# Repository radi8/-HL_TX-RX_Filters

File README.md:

# HL_TX-RX_Filters
Transmit and receive filters catalog plus Kicad layout for 100 x 100 mm PCB and part listings

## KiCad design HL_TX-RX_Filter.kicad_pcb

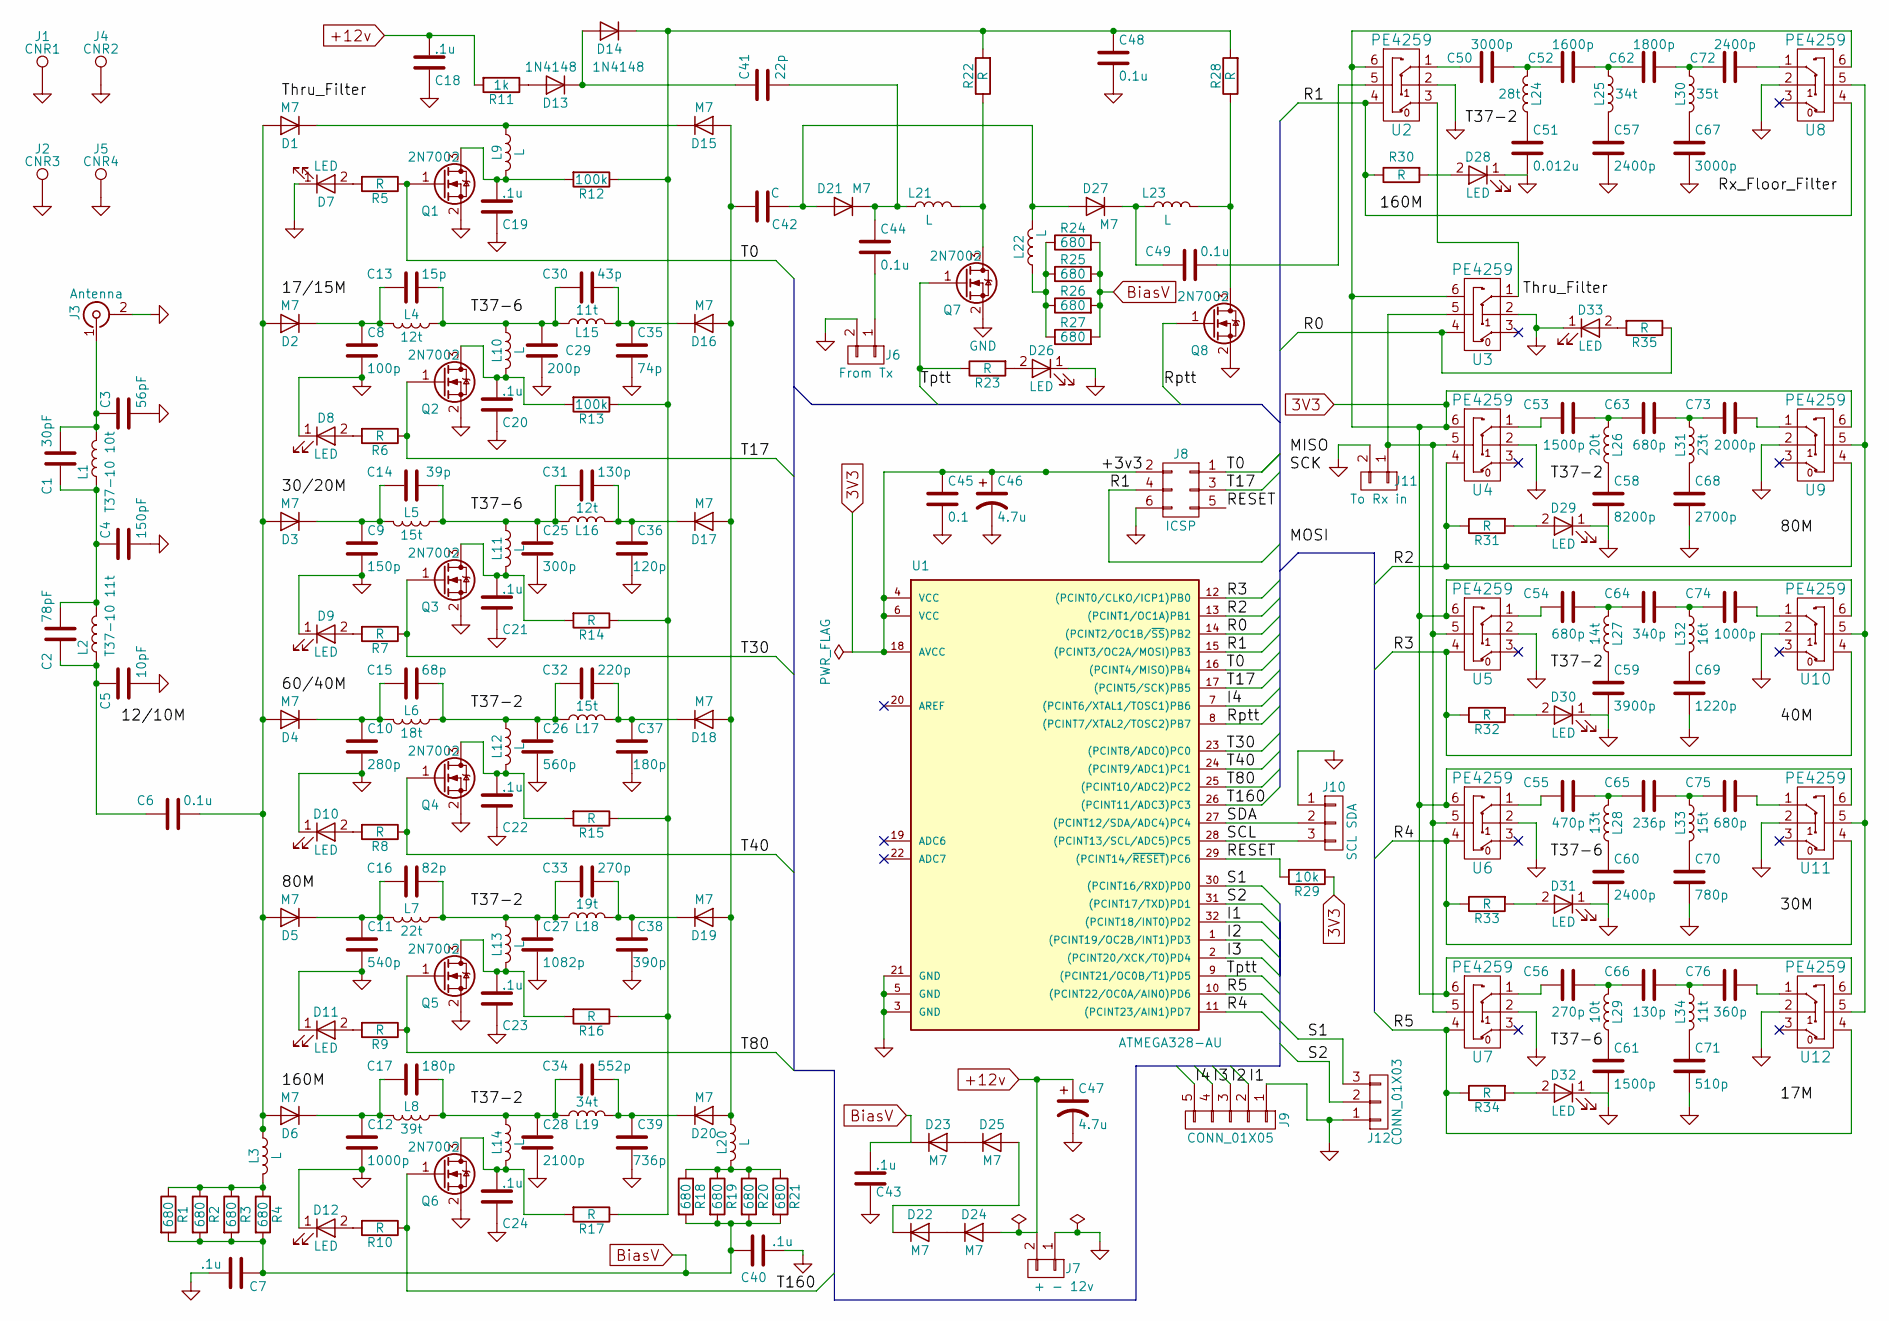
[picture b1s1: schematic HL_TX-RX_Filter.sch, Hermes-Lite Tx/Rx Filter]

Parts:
C1: 30pF; C_1206_HandSoldering
C2: 78pF; C_1206_HandSoldering
C3: 56pF; C_1206_HandSoldering
C4: 150pF; C_1206_HandSoldering
C5: 10pF; C_1206_HandSoldering
C6, C44, C48, C49: 0.1u; C_1206_HandSoldering
C7, C18, C19, C20, C21, C22, C23, C24, C40, C43: .1u; C_1206_HandSoldering
C8: 100p; C_1206_HandSoldering
C9: 150p; C_1206_HandSoldering
C10: 280p; C_1206_HandSoldering
C11: 540p; C_1206_HandSoldering
C12, C74: 1000p; C_1206_HandSoldering
C13: 15p; C_1206_HandSoldering
C14: 39p; C_1206_HandSoldering
C15: 68p; C_1206_HandSoldering
C16: 82p; C_1206_HandSoldering
C17, C37: 180p; C_1206_HandSoldering
C25: 300p; C_1206_HandSoldering
C26: 560p; C_1206_HandSoldering
C27: 1082p; C_1206_HandSoldering
C28: 2100p; C_1206_HandSoldering
C29: 200p; C_1206_HandSoldering
C30: 43p; C_1206_HandSoldering
C31, C66: 130p; C_1206_HandSoldering
C32: 220p; C_1206_HandSoldering
C33, C56: 270p; C_1206_HandSoldering
C34: 552p; C_1206_HandSoldering
C35: 74p; C_1206_HandSoldering
C36: 120p; C_1206_HandSoldering
C38: 390p; C_1206_HandSoldering
C39: 736p; C_1206_HandSoldering
C41: 22p; C_1206_HandSoldering
C42: C; C_1206_HandSoldering
C45: 0.1; C_1206_HandSoldering
C46, C47: 4.7u; CP_Radial_D5.0mm_P2.00mm
C50, C67: 3000p; C_1206_HandSoldering
C51: 0.012u; C_1206_HandSoldering
C52: 1600p; C_1206_HandSoldering
C53, C61: 1500p; C_1206_HandSoldering
C54, C63, C75: 680p; C_1206_HandSoldering
C55: 470p; C_1206_HandSoldering
C57, C60, C72: 2400p; C_1206_HandSoldering
C58: 8200p; C_1206_HandSoldering
C59: 3900p; C_1206_HandSoldering
C62: 1800p; C_1206_HandSoldering
C64: 340p; C_1206_HandSoldering
C65: 236p; C_1206_HandSoldering
C68: 2700p; C_1206_HandSoldering
C69: 1220p; C_1206_HandSoldering
C70: 780p; C_1206_HandSoldering
C71: 510p; C_1206_HandSoldering
C73: 2000p; C_1206_HandSoldering
C76: 360p; C_1206_HandSoldering
D1, D2, D3, D4, D5, D6, D15, D16, D17, D18, D19, D20, D21, D27: M7; D_SMA_Handsoldering
D7, D8, D9, D10, D11, D12, D26, D28, D29, D30, D31, D32, D33: LED; LED_1206
D13, D14: 1N4148; D_MiniMELF_Handsoldering
D22, D23, D24, D25: M7; D_SMA
J1: CNR1; 1pin
J2: CNR3; 1pin
J3: Antenna; SMAEDGE_TH
J4: CNR2; 1pin
J5: CNR4; 1pin
J6: From Tx; Pin_Header_Straight_1x02_Pitch2.54mm
J7: + - 12v; Pin_Header_Straight_1x02_Pitch2.54mm
J8: ICSP; Pin_Header_Straight_2x03_Pitch2.54mm
J9: CONN_01X05; Pin_Header_Straight_1x05_Pitch2.54mm
J10: SCL SDA; Pin_Header_Straight_1x03_Pitch2.54mm
J11: To Rx in; Pin_Header_Straight_1x02_Pitch2.54mm
J12: CONN_01X03; Pin_Header_Straight_1x03_Pitch2.54mm
L1: T37-10 10t; Toroid_T37_Vertical
L2: T37-10 11t; Toroid_T37_Vertical
L3, L9, L10, L11, L12, L13, L14, L20, L21, L22, L23: L; L_1812_HandSoldering
L4, L16: 12t; Toroid_T37_Vertical
L5, L17, L33: 15t; Toroid_T37_Vertical
L6: 18t; Toroid_T37_Vertical
L7: 22t; Toroid_T37_Vertical
L8: 39t; Toroid_T37_Vertical
L15, L34: 11t; Toroid_T37_Vertical
L18: 19t; Toroid_T37_Vertical
L19, L25: 34t; Toroid_T37_Vertical
L24: 28t; Toroid_T37_Vertical
L26: 20t; Toroid_T37_Vertical
L27: 14t; Toroid_T37_Vertical
L28: 13t; Toroid_T37_Vertical
L29: 10t; Toroid_T37_Vertical
L30: 35t; Toroid_T37_Vertical
L31: 23t; Toroid_T37_Vertical
L32: 16t; Toroid_T37_Vertical
Q1, Q2, Q3, Q4, Q5, Q6, Q7, Q8: 2N7002; SOT-23
R1, R2, R3, R4, R18, R19, R20, R21, R24, R25, R26, R27: 680; R_1206_HandSoldering
R5, R6, R7, R8, R9, R10, R14, R15, R16, R17, R22, R23, R28, R30, R31, R32, R33, R34, R35: R; R_1206_HandSoldering
R11: 1k; R_1206_HandSoldering
R12, R13: 100k; R_1206_HandSoldering
R29: 10k; R_1206_HandSoldering
U1: ATMEGA328-AU; TQFP-32_7x7mm_Pitch0.8mm
U2, U3, U4, U5, U6, U7, U8, U9, U10, U11, U12: PE4259; SOT-363_SC-70-6_Handsoldering

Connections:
3V3: C45.1, C46.1, J8.2, R29.1, U1.4 (VCC), U1.6 (VCC), U1.18 (AVCC), U2.6, U3.6, U4.6, U5.6, U6.6, U7.6, U8.6, U9.6, U10.6, U11.6, U12.6
+12v: C18.1, C47.1, D24.2 (A), J7.2, R11.2
/I1: J9.2, U1.32 ((PCINT18/INT0)PD2)
/I2: J9.3, U1.1 ((PCINT19/OC2B/INT1)PD3)
/I3: J9.4, U1.2 ((PCINT20/XCK/T0)PD4)
/I4: J9.5, U1.7 ((PCINT6/XTAL1/TOSC1)PB6)
/R0: R35.1, U1.14 ((PCINT2/OC1B/~SS~)PB2), U3.4
/R1: J8.4, R30.1, U1.15 ((PCINT3/OC2A/MOSI)PB3), U2.4, U8.4
/R2: R31.1, U1.13 ((PCINT1/OC1A)PB1), U4.4, U9.4
/R3: R32.1, U1.12 ((PCINT0/CLKO/ICP1)PB0), U5.4, U10.4
/R4: R33.1, U1.11 ((PCINT23/AIN1)PD7), U6.4, U11.4
/R5: R34.1, U1.10 ((PCINT22/OC0A/AIN0)PD6), U7.4, U12.4
/RESET: J8.5, R29.2, U1.29 ((PCINT14/~RESET~)PC6)
/Rptt: Q8.1 (G), U1.8 ((PCINT7/XTAL2/TOSC2)PB7)
/S1: J12.3, U1.30 ((PCINT16/RXD)PD0)
/S2: J12.2, U1.31 ((PCINT17/TXD)PD1)
/SCL: J10.3, U1.28 ((PCINT13/SCL/ADC5)PC5)
/SDA: J10.2, U1.27 ((PCINT12/SDA/ADC4)PC4)
/T0: J8.1, Q1.1 (G), R5.1, U1.16 ((PCINT4/MISO)PB4)
/T17: J8.3, Q2.1 (G), R6.1, U1.17 ((PCINT5/SCK)PB5)
/T30: Q3.1 (G), R7.1, U1.23 ((PCINT8/ADC0)PC0)
/T40: Q4.1 (G), R8.1, U1.24 ((PCINT9/ADC1)PC1)
/T80: Q5.1 (G), R9.1, U1.25 ((PCINT10/ADC2)PC2)
/T160: Q6.1 (G), R10.1, U1.26 ((PCINT11/ADC3)PC3)
/Tptt: Q7.1 (G), R23.1, U1.9 ((PCINT21/OC0B/T1)PD5)
BiasV: C7.2, C40.2, C43.1, D23.1 (K), R1.2, R2.2, R3.2, R4.2, R18.2, R19.2, R20.2, R21.2, R24.2, R25.2, R26.2, R27.2
GND: C3.2, C4.2, C5.2, C7.1, C8.2, C9.2, C10.2, C11.2, C12.2, C18.2, C19.2, C20.2, C21.2, C22.2, C23.2, C24.2, C25.2, C26.2, C27.2, C28.2, C29.2, C35.2, C36.2, C37.2, C38.2, C39.2, C40.1, C43.2, C45.2, C46.2, C47.2, C48.2, C51.2, C57.2, C58.2, C59.2, C60.2, C61.2, C67.2, C68.2, C69.2, C70.2, C71.2, D7.1 (K), D8.1 (K), D9.1 (K), D10.1 (K), D11.1 (K), D12.1 (K), D26.1 (K), D28.1 (K), D29.1 (K), D30.1 (K), D31.1 (K), D32.1 (K), D33.1 (K), J1.1, J2.1, J3.2 (Ext), J4.1, J5.1, J6.2, J7.1, J8.6, J9.1, J10.1, J11.2, J12.1, Q1.2 (S), Q2.2 (S), Q3.2 (S), Q4.2 (S), Q5.2 (S), Q6.2 (S), Q7.2 (S), Q8.2 (S), U1.3 (GND), U1.5 (GND), U1.21 (GND), U2.2, U3.2, U4.2, U5.2, U6.2, U7.2, U8.2, U9.2, U10.2, U11.2, U12.2
unnamed: C1.1, C2.2, C4.1, L1.1, L2.2
unnamed: C1.2, C3.1, J3.1 (In), L1.2
unnamed: C2.1, C5.1, C6.1, L2.1
unnamed: C6.2, D1.2 (A), D2.2 (A), D3.2 (A), D4.2 (A), D5.2 (A), D6.2 (A), L3.1
unnamed: C10.1, C15.1, D4.1 (K), L6.2
unnamed: C11.1, C16.1, D5.1 (K), L7.2
unnamed: C12.1, C17.1, D6.1 (K), L8.2
unnamed: C8.1, C13.1, D2.1 (K), L4.2
unnamed: C13.2, C29.1, C30.1, L4.1, L10.1, L15.1
unnamed: C9.1, C14.1, D3.1 (K), L5.2
unnamed: C14.2, C25.1, C31.1, L5.1, L11.1, L16.1
unnamed: C15.2, C26.1, C32.1, L6.1, L12.1, L17.1
unnamed: C16.2, C27.1, C33.1, L7.1, L13.1, L18.1
unnamed: C17.2, C28.1, C34.1, L8.1, L14.1, L19.1
unnamed: C19.1, L9.2, Q1.3 (D), R12.2
unnamed: C20.1, L10.2, Q2.3 (D), R13.2
unnamed: C21.1, L11.2, Q3.3 (D), R14.2
unnamed: C22.1, L12.2, Q4.3 (D), R15.2
unnamed: C23.1, L13.2, Q5.3 (D), R16.2
unnamed: C24.1, L14.2, Q6.3 (D), R17.2
unnamed: C30.2, C35.1, D16.1 (K), L15.2
unnamed: C31.2, C36.1, D17.1 (K), L16.2
unnamed: C32.2, C37.1, D18.1 (K), L17.2
unnamed: C33.2, C38.1, D19.1 (K), L18.2
unnamed: C34.2, C39.1, D20.1 (K), L19.2
unnamed: C41.1, D13.1 (K), D14.2 (A)
unnamed: C41.2, C44.1, D21.1 (K), L21.1
unnamed: C42.1, D15.2 (A), D16.2 (A), D17.2 (A), D18.2 (A), D19.2 (A), D20.2 (A), L20.1
unnamed: C42.2, D21.2 (A), D27.2 (A), L22.2
unnamed: C44.2, J6.1
unnamed: C48.1, D14.1 (K), R12.1, R13.1, R14.1, R15.1, R16.1, R17.1, R22.2, R28.2
unnamed: C49.1, D27.1 (K), L23.1
unnamed: C49.2, U2.5
unnamed: C50.1, U2.1
unnamed: C50.2, C52.1, L24.2
unnamed: C51.1, L24.1
unnamed: C52.2, C62.1, L25.1
unnamed: C53.1, U4.1
unnamed: C53.2, C63.1, L26.2
unnamed: C54.1, U5.1
unnamed: C54.2, C64.1, L27.2
unnamed: C55.1, U6.1
unnamed: C55.2, C65.1, L28.2
unnamed: C56.1, U7.1
unnamed: C56.2, C66.1, L29.2
unnamed: C57.1, L25.2
unnamed: C58.1, L26.1
unnamed: C59.1, L27.1
unnamed: C60.1, L28.1
unnamed: C61.1, L29.1
unnamed: C62.2, C72.1, L30.1
unnamed: C63.2, C73.1, L31.1
unnamed: C64.2, C74.1, L32.1
unnamed: C65.2, C75.1, L33.1
unnamed: C66.2, C76.1, L34.1
unnamed: C67.1, L30.2
unnamed: C68.1, L31.2
unnamed: C69.1, L32.2
unnamed: C70.1, L33.2
unnamed: C71.1, L34.2
unnamed: C72.2, U8.1
unnamed: C73.2, U9.1
unnamed: C74.2, U10.1
unnamed: C75.2, U11.1
unnamed: C76.2, U12.1
unnamed: D1.1 (K), D15.1 (K), L9.1
unnamed: D7.2 (A), R5.2
unnamed: D8.2 (A), R6.2
unnamed: D9.2 (A), R7.2
unnamed: D10.2 (A), R8.2
unnamed: D11.2 (A), R9.2
unnamed: D12.2 (A), R10.2
unnamed: D13.2 (A), R11.1
unnamed: D22.1 (K), D25.2 (A)
unnamed: D22.2 (A), D24.1 (K)
unnamed: D23.2 (A), D25.1 (K)
unnamed: D26.2 (A), R23.2
unnamed: D28.2 (A), R30.2
unnamed: D29.2 (A), R31.2
unnamed: D30.2 (A), R32.2
unnamed: D31.2 (A), R33.2
unnamed: D32.2 (A), R34.2
unnamed: D33.2 (A), R35.2
unnamed: J11.1, U3.5, U4.5, U5.5, U6.5, U7.5
unnamed: L3.2, R1.1, R2.1, R3.1, R4.1
unnamed: L20.2, R18.1, R19.1, R20.1, R21.1
unnamed: L21.2, Q7.3 (D), R22.1
unnamed: L22.1, R24.1, R25.1, R26.1, R27.1
unnamed: L23.2, Q8.3 (D), R28.1
unnamed: U2.3, U3.1
unnamed: U8.5, U9.5, U10.5, U11.5, U12.5

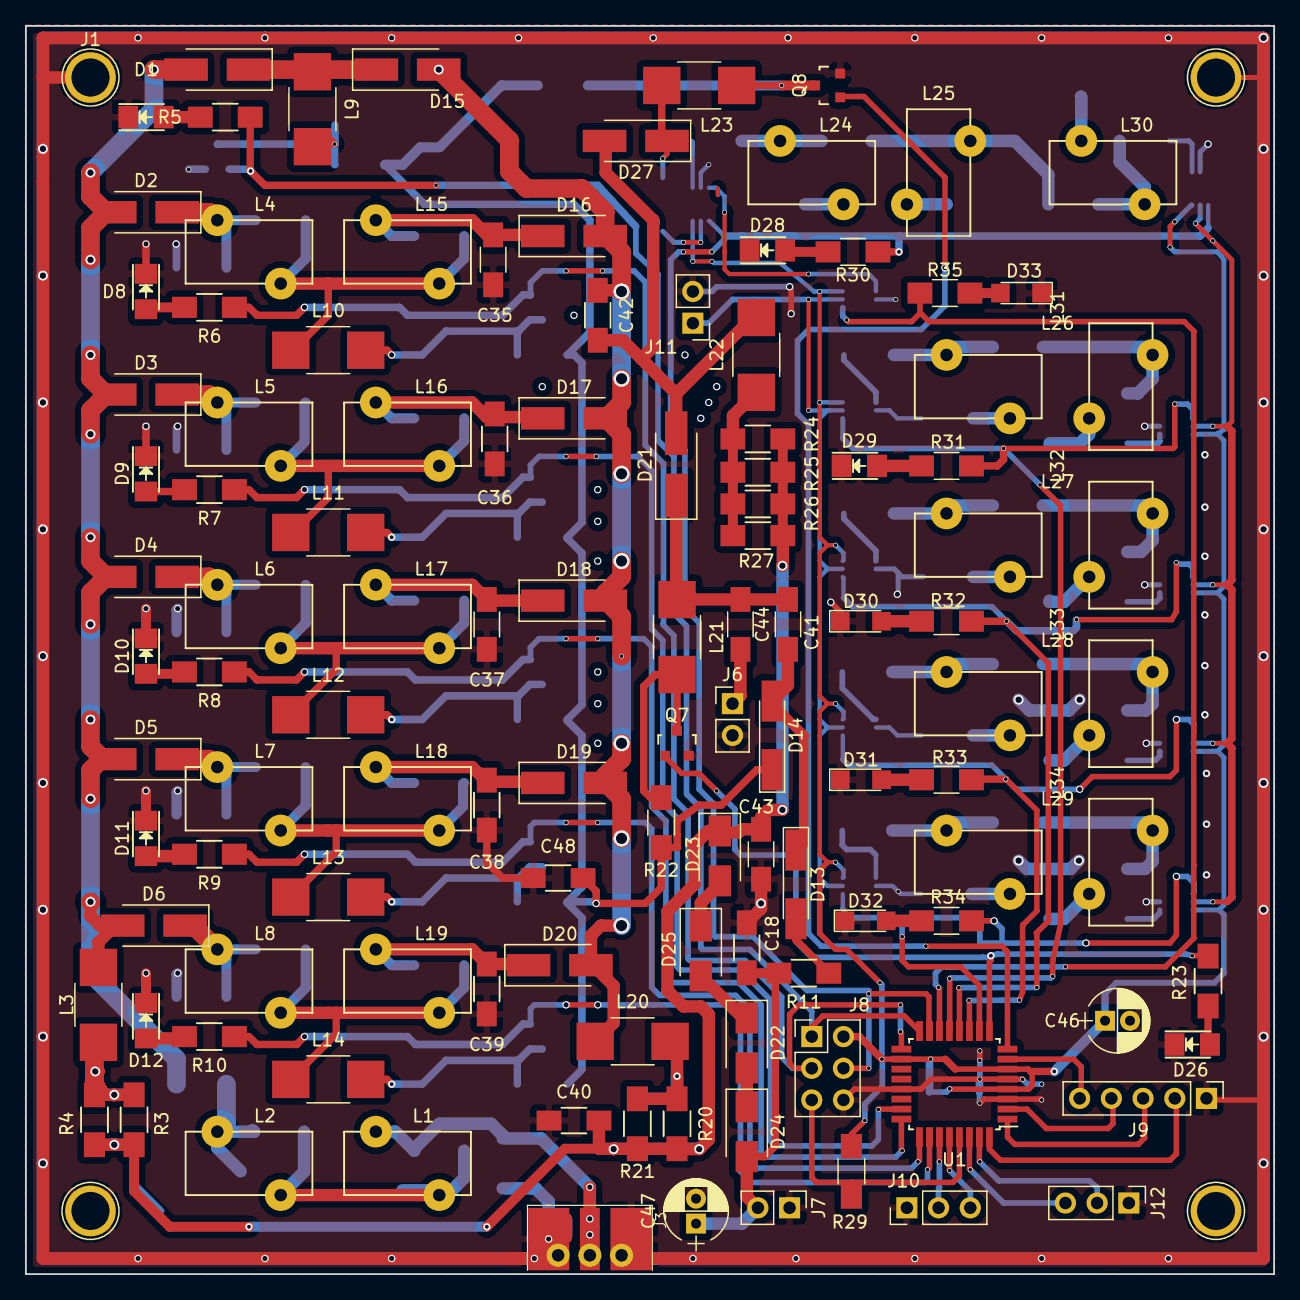
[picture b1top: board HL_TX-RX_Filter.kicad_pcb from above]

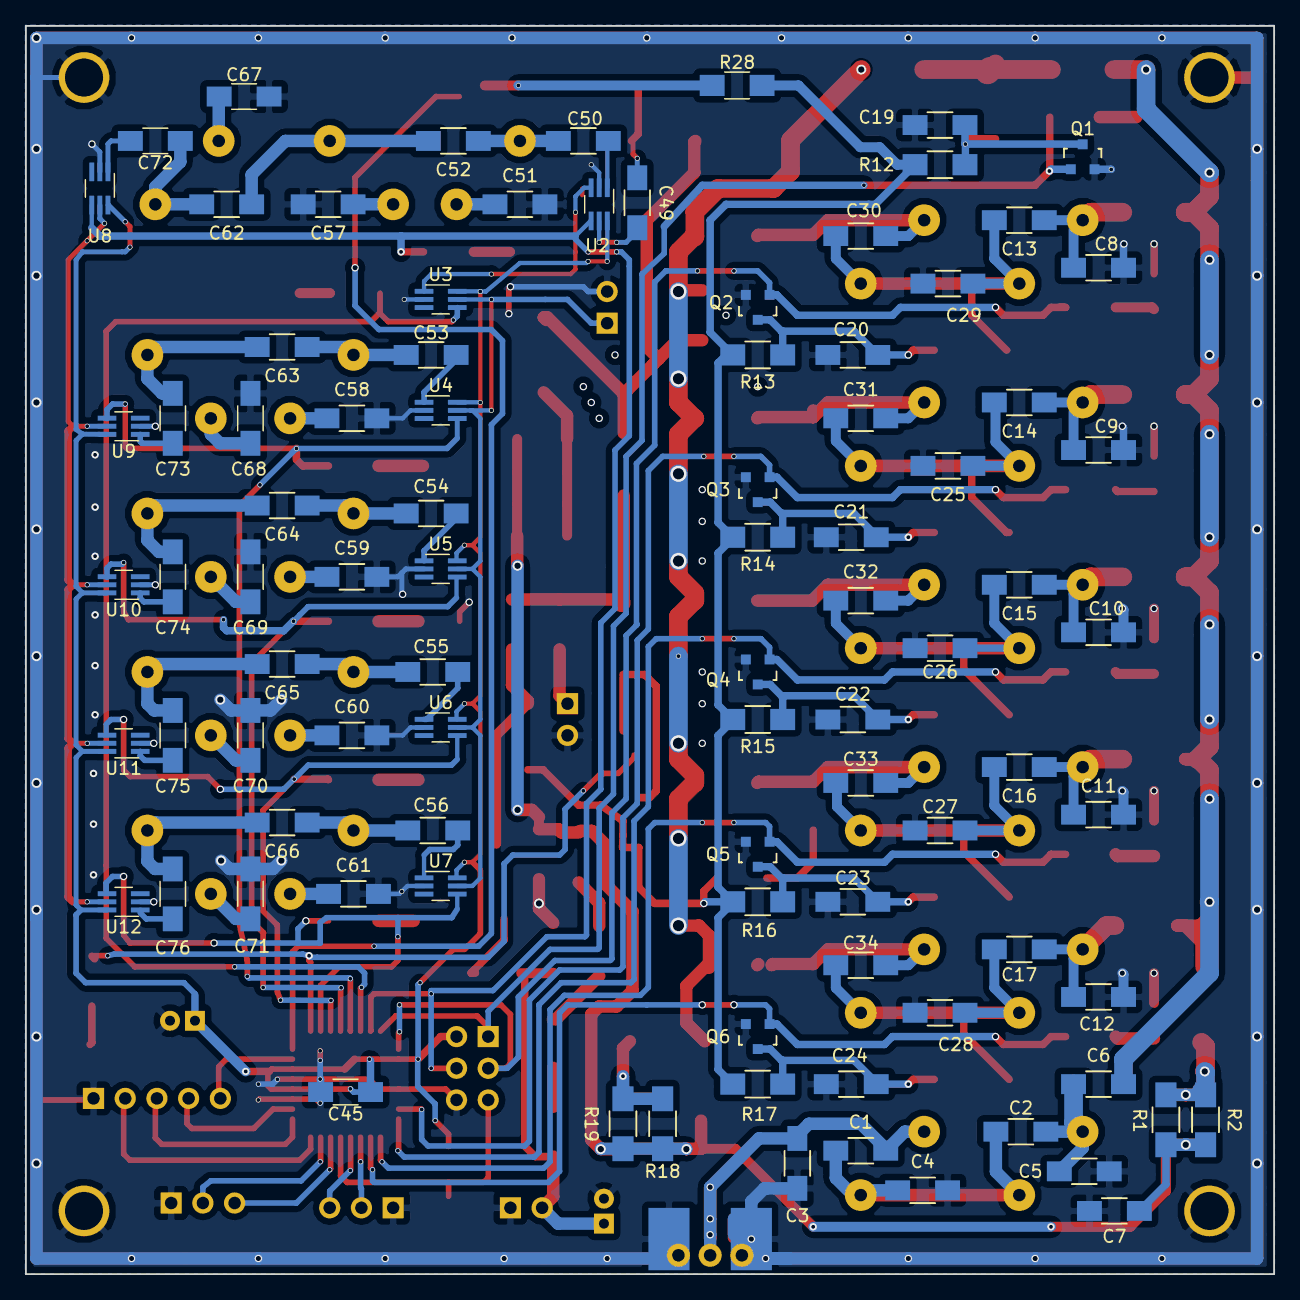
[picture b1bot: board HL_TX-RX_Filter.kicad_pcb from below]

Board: 2 copper layers, 100.0 x 100.0 mm, 210 parts (90 on the bottom side), 118 nets.

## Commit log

2017-05-09 Added README.md
2017-05-09 Drawn in roofing filter and through diodes
2017-05-10 Totalled up capacitors
2017-05-10 Updated capacitor values
2017-05-11 Tweaking capacitor values
2017-05-12 Working on BOM
2017-05-13 Progress on schematic
2017-05-18 Added ICSP circuitry
2017-05-18 Added Tx LED indicators and ptt wiring
2017-06-13 minor layout changes
2017-07-05 Added 60/40M to Tx filter catalog
2017-07-06 Changes to ISP wiring
2017-07-07 Added new page layout file
2017-07-07 Tweaks to page layout file
2017-07-12 Corrections and further additions
2017-07-12 Diode switching experiment added
2017-07-13 Further progress on PCB
2017-07-13 Added information on cascaded filters
2017-07-13 Linked footprints with CvPcb
2017-07-14 Progressing with board layout
2017-07-16 Organising the project and other housekeeping
2017-07-16 Resized toroids and M7 diodes
2017-07-17 Minor changes
2017-07-17 Work on Tx Filter layout
2017-07-17 More Tx filter layout
2017-07-18 More Tx layout and choke footprint mods
2017-07-18 Claudio's PA harmonic measurements added to resource
2017-07-19 More progress with Tx filter board layout
2017-07-20 Further progress on layout
2017-07-20 Rearranging pins on microprocessor to better fit layout
2017-07-21 Sorted out some footprints
2017-07-21 Squeezed up Tx filters to hold 30M filter
2017-07-21 Re-annotated board
2017-07-22 Re-building PCB after annotation redo
2017-07-22 Rearranging layout for re-annotated schematic
2017-07-23 More layout progress
2017-07-23 Working on laying out Receive Filters
2017-07-23 Wiring of Rx filters
2017-07-23 Laying tracks for Tx switching
2017-07-24 Further progress on Filter switching lines
2017-07-26 Placing inputs to microprocessor
2017-07-29 Adjusted toroid sizes
2017-07-29 Added Jim's filters
2017-07-30 Removed surplus choke etc from TX, RX switch
2017-07-31 Changed to Bourns chokes and progressed layout
2017-08-01 Add Tx/Rx changeover components
2017-08-01 More layout around bias voltage area
2017-08-01 Got last of components placed on board
2017-08-01 Saving state before complete annotate of schematic
2017-08-02 Reorganizing the components after annotate done
2017-08-02 Continuing layout
2017-08-03 Nearly there
2017-08-03 All DRC checks are now OK
2017-08-04 Fabricated and prepared Gerbers
2017-09-05 Corrections to filter values
2017-09-05 Fixed merge problems
2017-09-06 Replaced accidently deleted Tx filter catalog
2017-09-06 Added plot files and updated Tx filter catalog
2017-10-29 Terminated PE4259s and annotated more components
2018-06-28 Filter plots worked on
2018-06-28 Rearrange filters
2018-06-28 Filter tests etc
2018-06-28 Added further files
2018-06-29 Aligning masters
2018-06-29 Added HL_TX-RX_Filter.pro
2018-06-29 Tx filters config changed
2018-06-29 Progressing new filter design
2018-06-30 Some tweaks
2018-06-30 More tweaks
2018-07-06 Altered to piggy back on HL2 board
2018-09-30 Upgraded to Kicad ver 5
2018-11-02 Changes to match HL2 pinouts
